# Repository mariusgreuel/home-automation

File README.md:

# Marius Home Automation projects

This repository contains various projects that I use in my home:

- [Smart-Meter Gateway](./smartmeter-gateway/): A ESPHOME gateway for reading smart meters, gas meters, and water meters.
- [Smart-Meter Reading Head](./smartmeter-reading-head/): An optical reading head for smart meters.
- [Gas Meter Sensor](./gas-meter-sensor/): A 3D model for a gas meter sensor mount.
- [Water Meter Sensor](./water-meter-sensor/): A 3D model for a water meter sensor mount.

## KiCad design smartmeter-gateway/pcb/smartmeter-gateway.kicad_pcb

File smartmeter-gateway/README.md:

# Smart-Meter Gateway

This repository contains the KiCad schematic and PCB design of a smart-meter gateway.

The gateway includes multiple I/O ports, including a serial port for a smart meter reading head,
and some general purpose GPIO pins for hall sensors or other sensors.

The PCB is designed to work with a [Seeed Studio XIAO ESP32C3](https://wiki.seeedstudio.com/XIAO_ESP32C3_Getting_Started/),
and fits into a [Hammond 1551KGY](https://www.hammfg.com/part/1551KGY) enclosure.

The design includes optional components such as pull-up resistors or ESD protection diodes
that you may populate depending on your needs.

I use the [ESPHome](https://esphome.io/) firmware to read the data from the sensors and send it to my home automation system.

## Overview

Finished smartmeter gateway:

Front view of PCB:

Back view of PCB:

## Software

To read and publish the data to your home automation software,
you may use the [ESPHome](https://esphome.io/) firmware and the [Home Assistant](https://www.home-assistant.io/) software.

This repository contains an example configuration [`esphome/esphome-smart-meter.yaml`](./esphome/esphome-smart-meter.yaml) for the ESPHome software,
which includes the following features:

- Reading SML data from a smart meter reading head
- Reading data from a gas meter via a hall sensor
- Reading data from a water meter via a hall sensor
- Setting the initial value of the gas and water meters via the web interface

Note that you need to edit the ESPHome secrets file [`esphome/secrets.yaml`](./esphome/secrets.yaml)
and enter your WiFi credentials and generate new OTA and [API keys](https://esphome.io/components/api.html):

When you have [installed ESPHome](https://esphome.io/guides/installing_esphome.html) on your computer,
you can use the following command to install the firmware on your computer:

```console
esphome run esphome-smart-meter.yaml
```

When the smartmeter gateway is connected to your WiFi network, the device should be discovered automatically by Home Assistant.

## License

All files are released under the GNU GPLv3.

Copyright 2024 Marius Greuel.

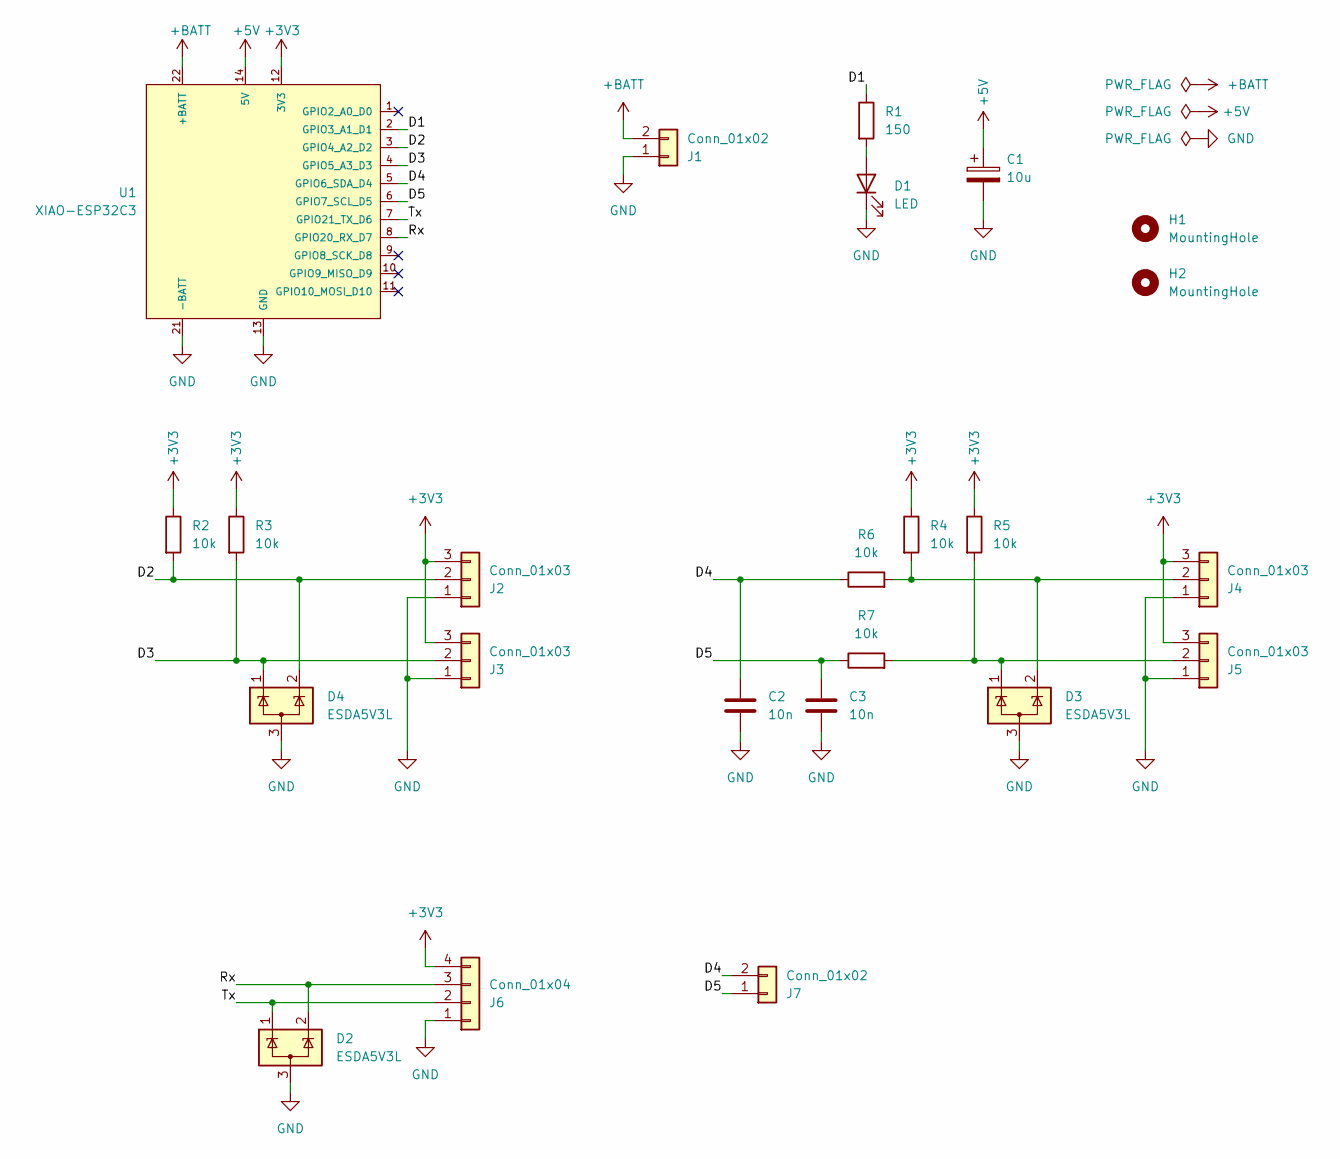
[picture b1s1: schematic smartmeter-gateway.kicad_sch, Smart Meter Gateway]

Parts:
C1: 10u; CP_EIA-6032-28_Kemet-C
C2, C3: 10n; C_0805_2012Metric
D1: LED; LED_0805_2012Metric
D2, D3, D4: ESDA5V3L; SOT-23-3
H1, H2: MountingHole; MountingHole_2.5mm
J1, J7: Conn_01x02; PinHeader_1x02_P2.54mm_Vertical
J2, J3, J4, J5: Conn_01x03; PinHeader_1x03_P2.54mm_Vertical
J6: Conn_01x04; PinHeader_1x04_P2.54mm_Vertical
R1: 150; R_0805_2012Metric
R2, R3, R4, R5, R6, R7: 10k; R_0805_2012Metric
U1: XIAO-ESP32C3; Seeed Studio XIAO

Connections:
+3V3: J2.3, J3.3, J4.3, J5.3, J6.4, R2.1, R3.1, R4.1, R5.1, U1.12 (3V3)
+5V: C1.1, U1.14 (5V)
+BATT: J1.2, U1.22 (+BATT)
/D1: R1.1, U1.2 (GPIO3_A1_D1)
/D2: D4.2 (K), J2.2, R2.2, U1.3 (GPIO4_A2_D2)
/D3: D4.1 (K), J3.2, R3.2, U1.4 (GPIO5_A3_D3)
/D4: C2.1, J7.2, R6.1, U1.5 (GPIO6_SDA_D4)
/D5: C3.1, J7.1, R7.1, U1.6 (GPIO7_SCL_D5)
/Rx: D2.2 (K), J6.3, U1.8 (GPIO20_RX_D7)
/Tx: D2.1 (K), J6.2, U1.7 (GPIO21_TX_D6)
GND: C1.2, C2.2, C3.2, D1.1 (K), D2.3 (A), D3.3 (A), D4.3 (A), J1.1, J2.1, J3.1, J4.1, J5.1, J6.1, U1.13 (GND), U1.21 (-BATT)
unnamed: D1.2 (A), R1.2
unnamed: D3.2 (K), J4.2, R4.2, R6.2
unnamed: D3.1 (K), J5.2, R5.2, R7.2

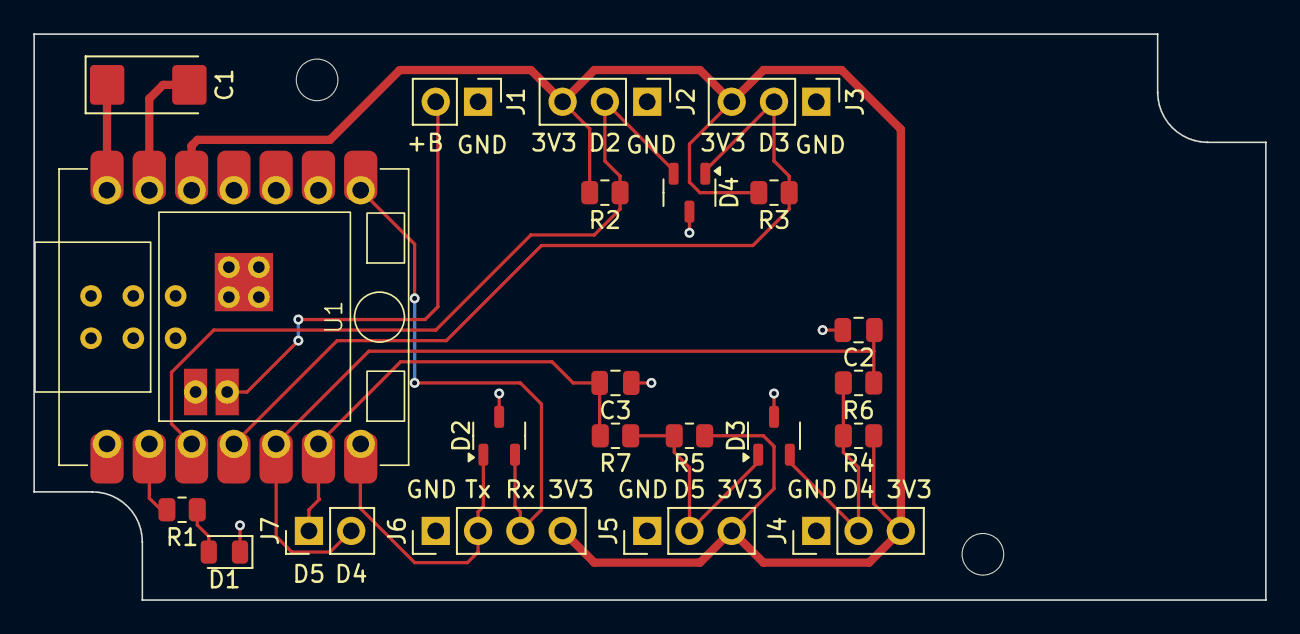
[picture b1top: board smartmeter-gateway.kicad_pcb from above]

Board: 2 copper layers, 74.0 x 34.0 mm, 24 parts (0 on the bottom side), 14 nets.

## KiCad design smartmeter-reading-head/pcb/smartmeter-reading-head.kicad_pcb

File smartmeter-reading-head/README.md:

# Smart-Meter Reading Head

This repository contains the KiCad schematic and PCB design of a smart-meter reading head,
as well as a 3D model of the reading head.

The reading head is designed to be used for electricity meters following the IEC 62056-21 specification,
which includes an optical interface.

The PCB includes a serial port and runs on a 3.3V power supply.

To read and publish the data to your home automation software,
you may use this [smart meter gateway](../smartmeter-gateway/).

## Overview

Front view of PCB:

Back view of PCB:

Section cut of 3D model:

Sensor mounted to the electricity meter:

## Files

- [KiCad project](./pcb/)
- [Fusion 360 3D model including STL and STEP files](./models/)

## License

All files are released under the GNU GPLv3.

Copyright 2024 Marius Greuel.

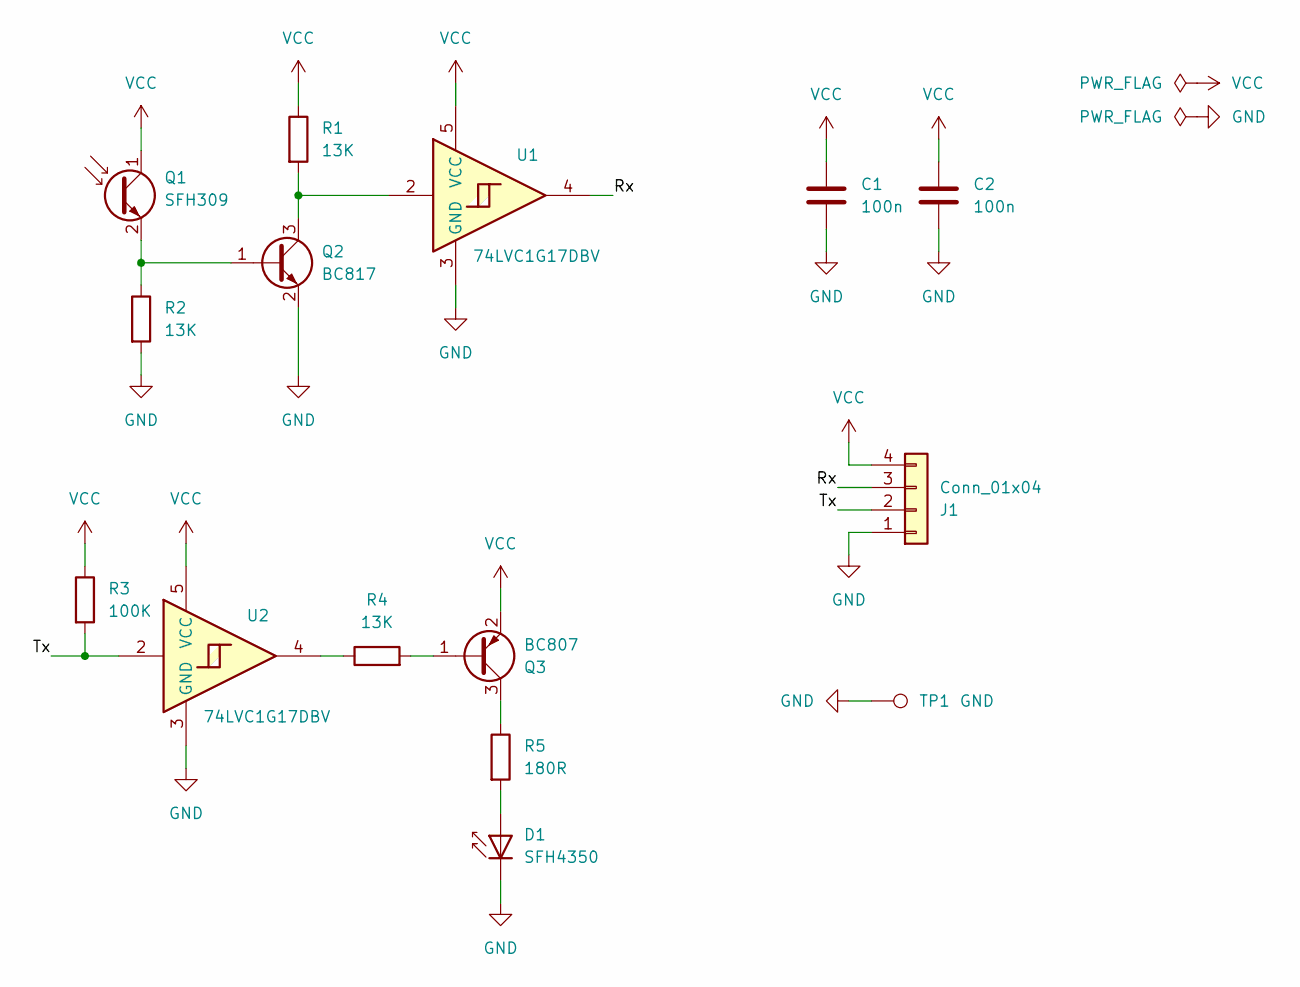
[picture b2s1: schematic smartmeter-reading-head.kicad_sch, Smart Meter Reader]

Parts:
C1, C2: 100n; C_0805_2012Metric
D1: SFH4350; LED_D3.0mm_IRBlack
J1: Conn_01x04; PinHeader_1x04_P2.54mm_Vertical
Q1: SFH309; LED_D3.0mm_Clear
Q2: BC817; SOT-23
Q3: BC807; SOT-23
R1, R2, R4: 13K; R_0805_2012Metric
R3: 100K; R_0805_2012Metric
R5: 180R; R_0805_2012Metric
TP1: GND; TestPoint_Pad_D1.0mm
U1, U2: 74LVC1G17DBV; SOT-23-5

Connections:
/Rx: J1.3, U1.4
/Tx: J1.2, R3.2, U2.2
GND: C1.2, C2.2, D1.1 (K), J1.1, Q2.2 (E), R2.2, TP1.1, U1.3 (GND), U2.3 (GND)
unnamed: D1.2 (A), R5.2
unnamed: Q1.2 (E), Q2.1 (B), R2.1
unnamed: Q2.3 (C), R1.2, U1.2
unnamed: Q3.1 (B), R4.2
unnamed: Q3.3 (C), R5.1
unnamed: R4.1, U2.4
VCC: C1.1, C2.1, J1.4, Q1.1 (C), Q3.2 (E), R1.1, R3.1, U1.5 (VCC), U2.5 (VCC)

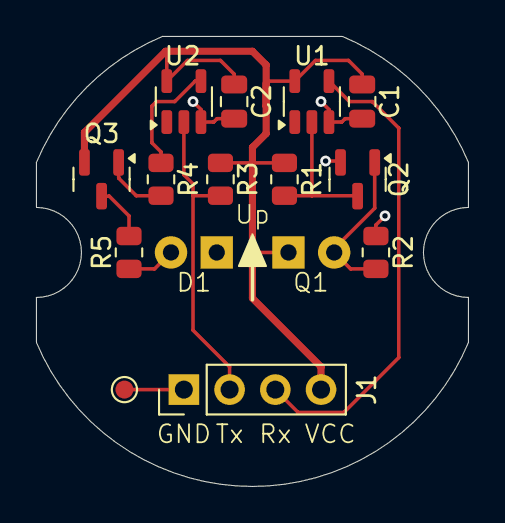
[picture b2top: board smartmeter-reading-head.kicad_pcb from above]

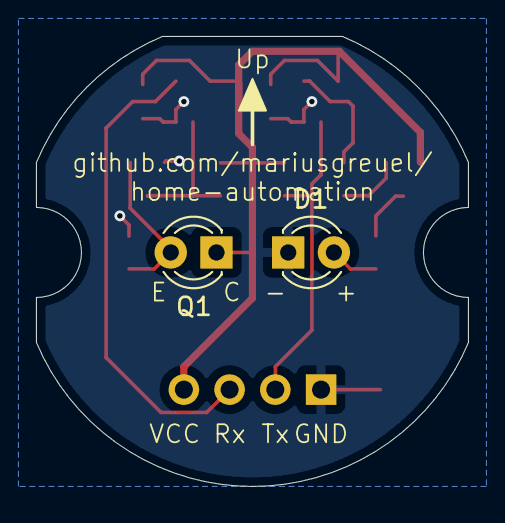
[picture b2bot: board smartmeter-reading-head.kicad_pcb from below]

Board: 2 copper layers, 24.0 x 25.0 mm, 15 parts (2 on the bottom side), 10 nets.

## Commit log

2025-04-15 Add more pictures and 3D models

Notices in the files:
smartmeter-gateway/pcb/smartmeter-gateway.kicad_pcb:
© 2024 Marius Greuel
